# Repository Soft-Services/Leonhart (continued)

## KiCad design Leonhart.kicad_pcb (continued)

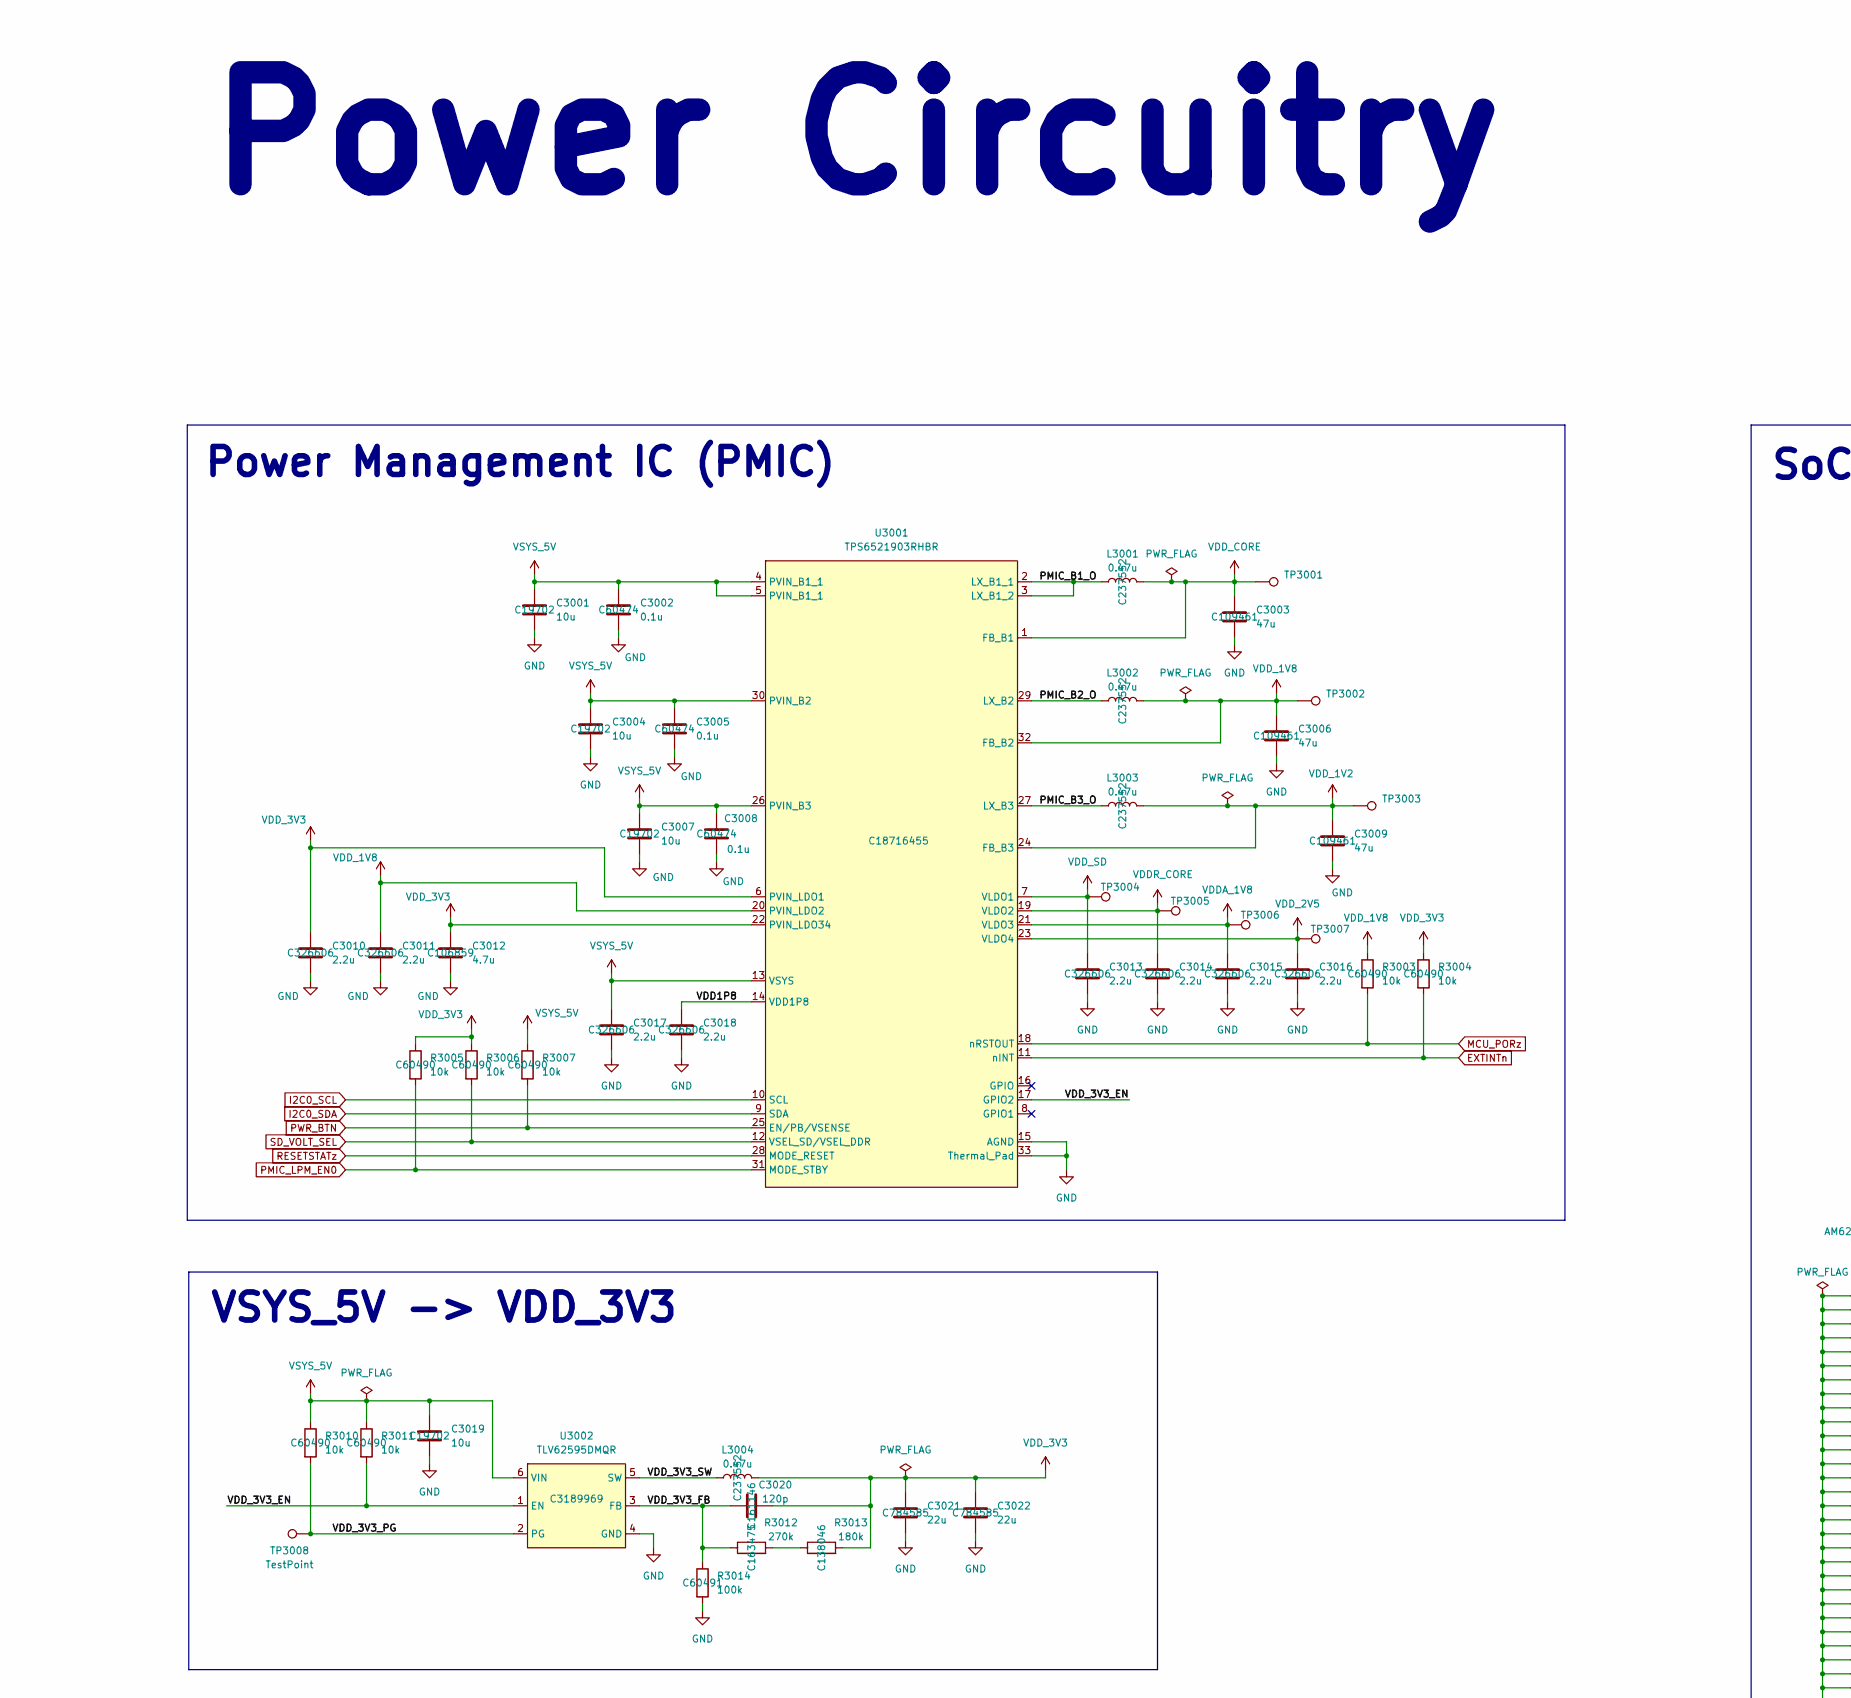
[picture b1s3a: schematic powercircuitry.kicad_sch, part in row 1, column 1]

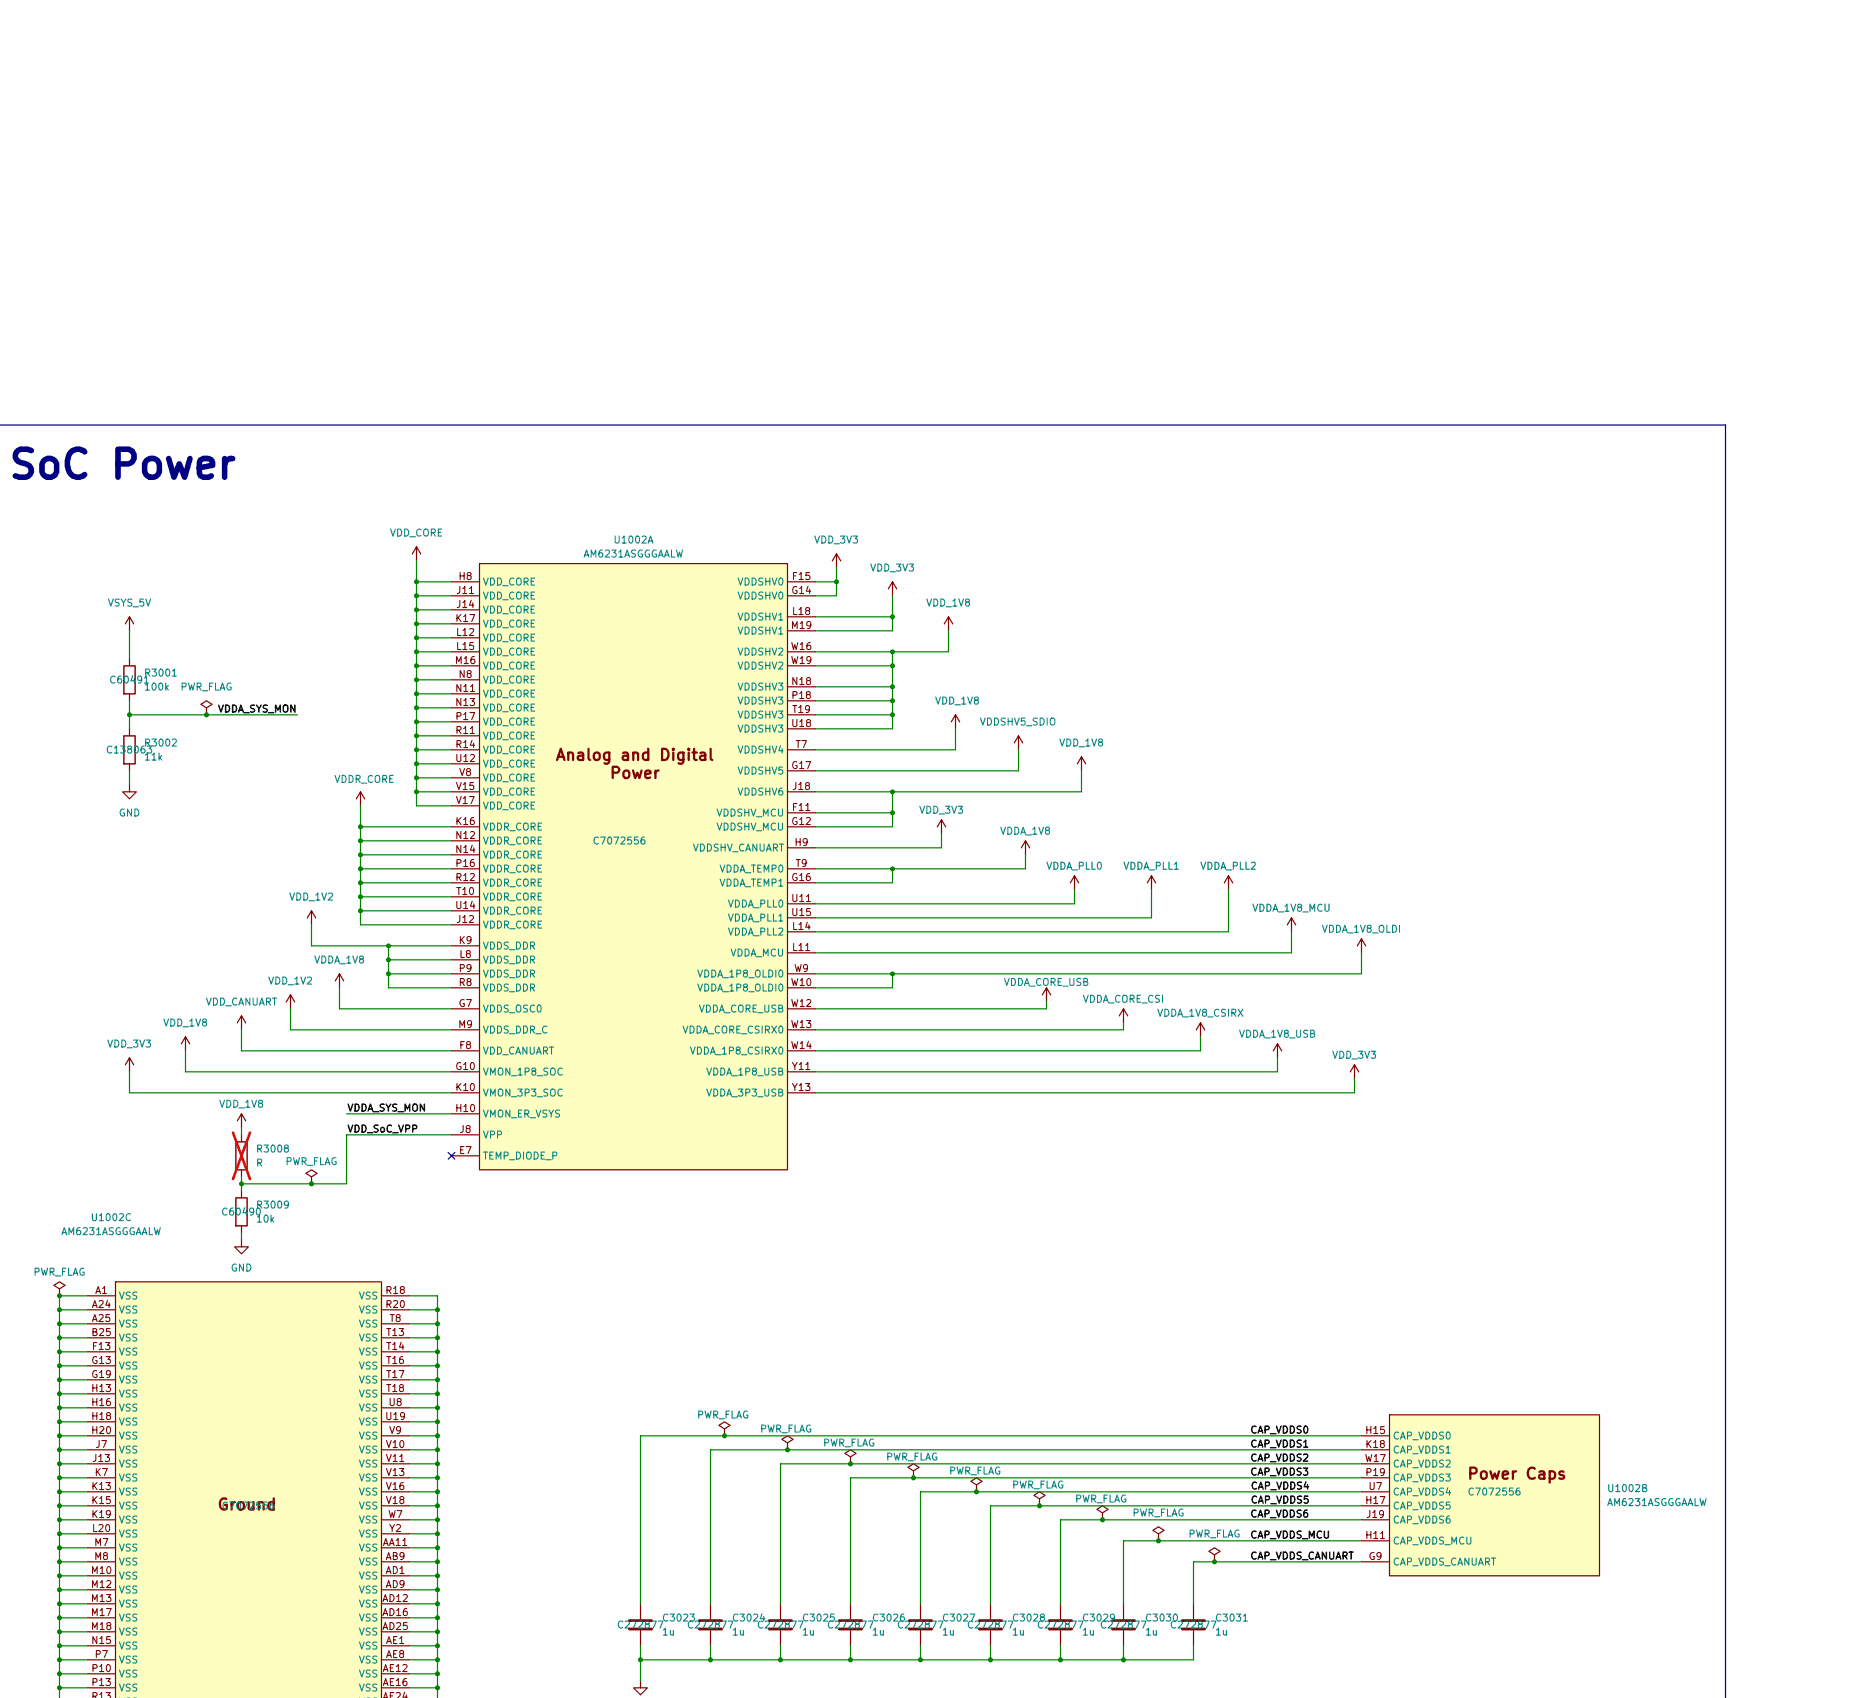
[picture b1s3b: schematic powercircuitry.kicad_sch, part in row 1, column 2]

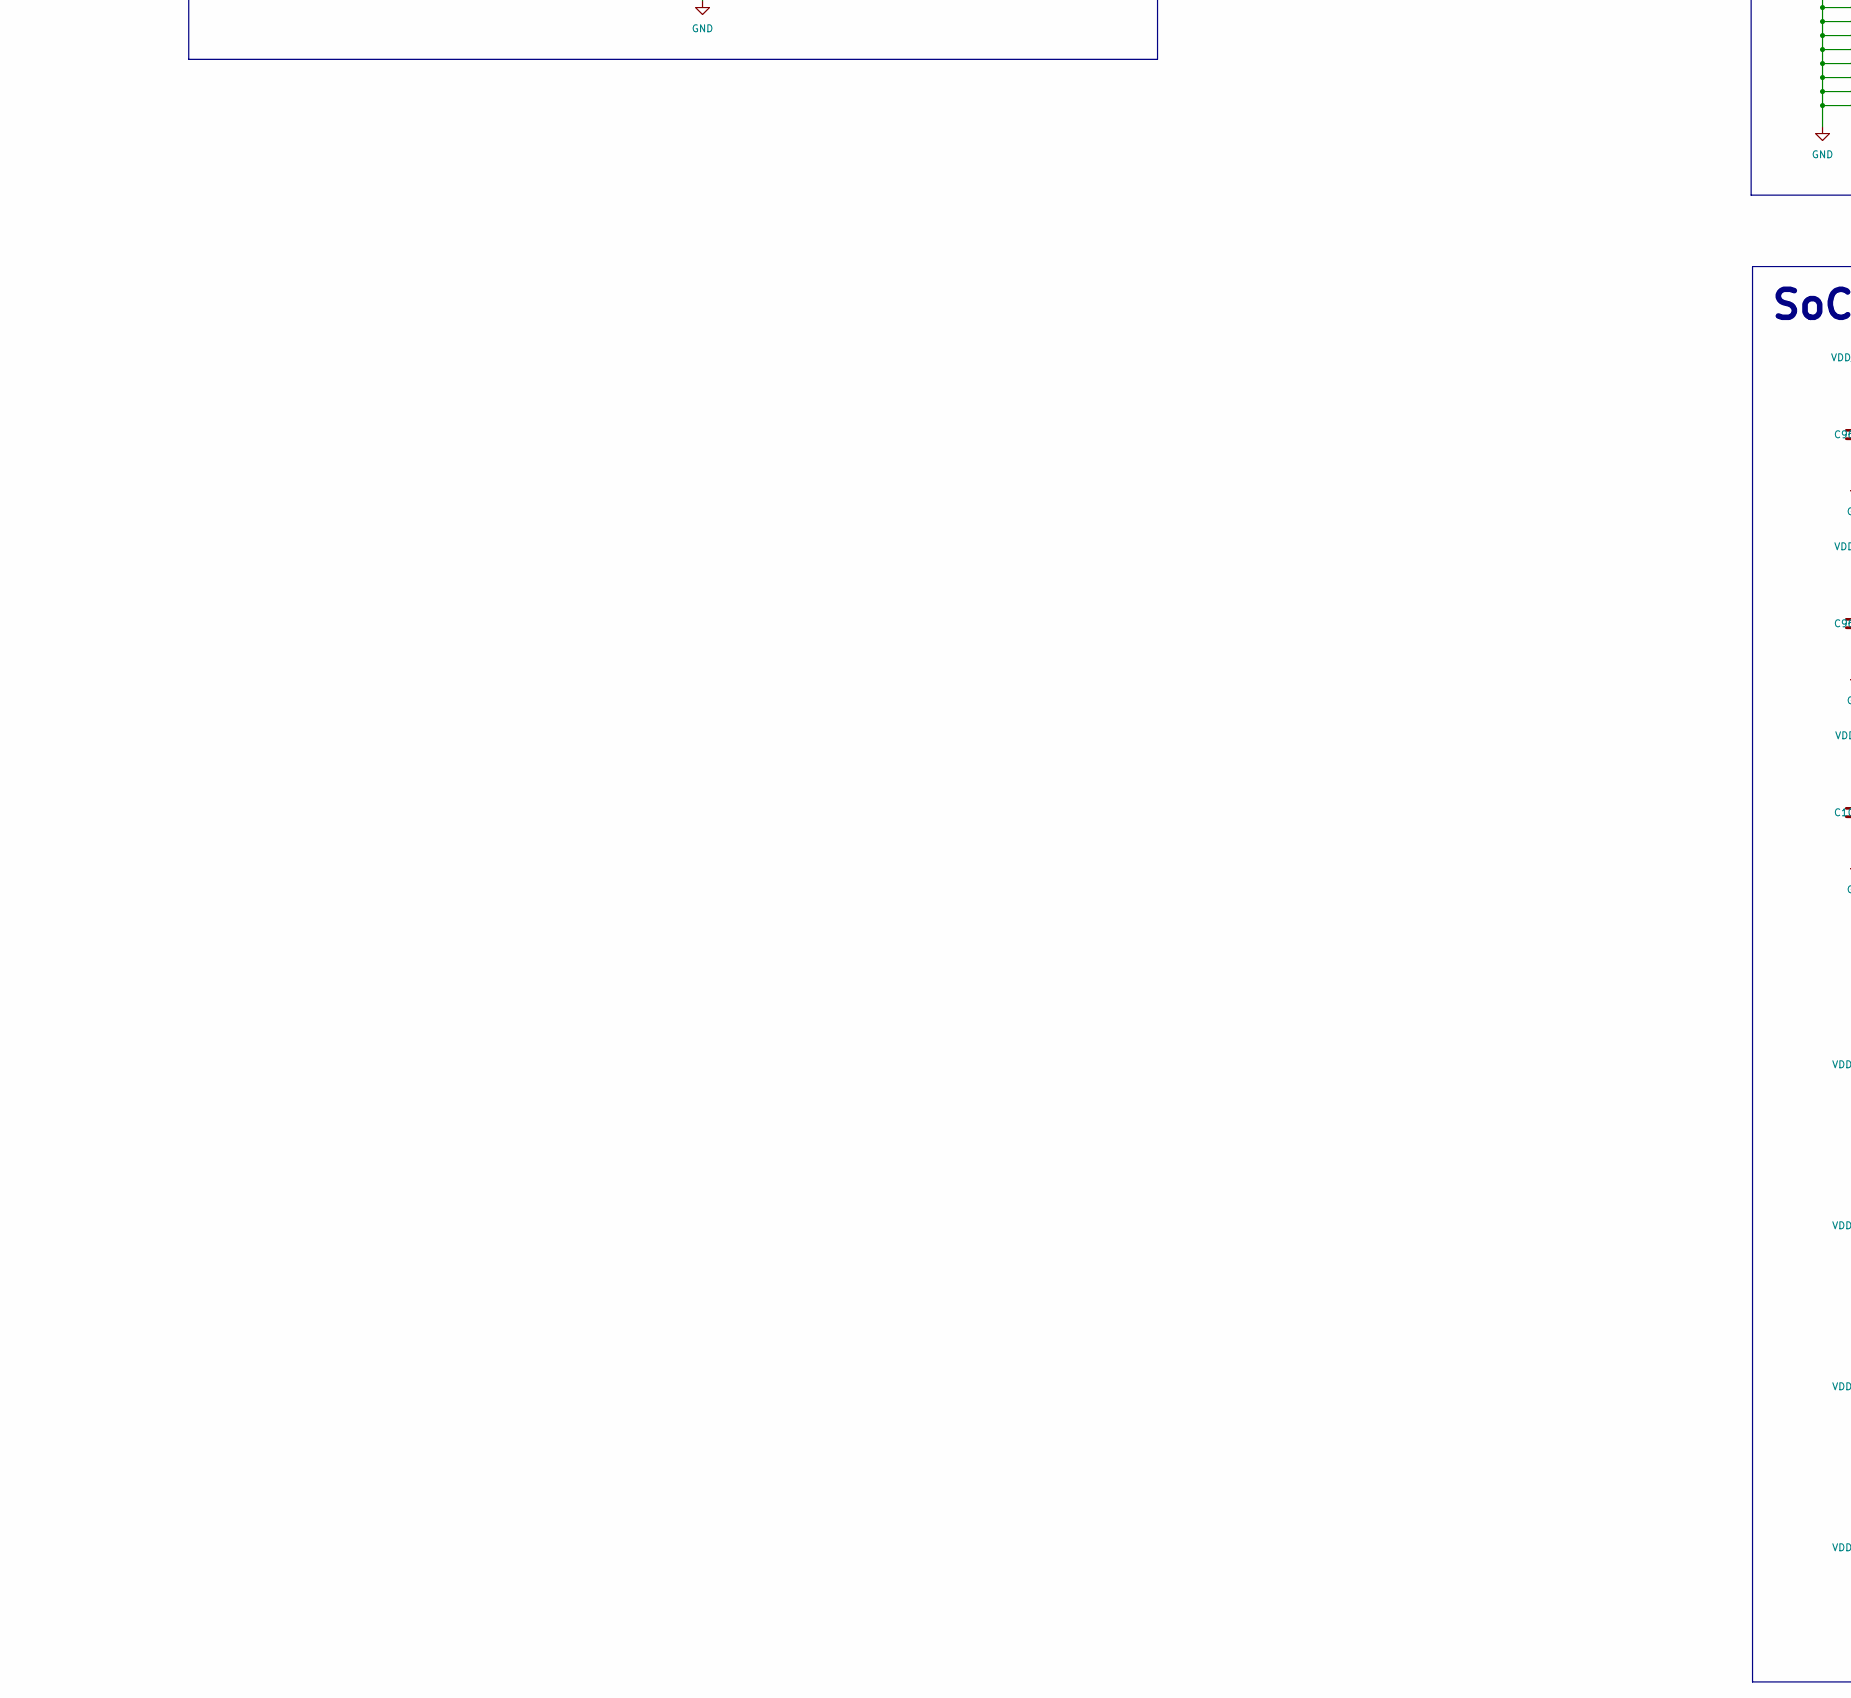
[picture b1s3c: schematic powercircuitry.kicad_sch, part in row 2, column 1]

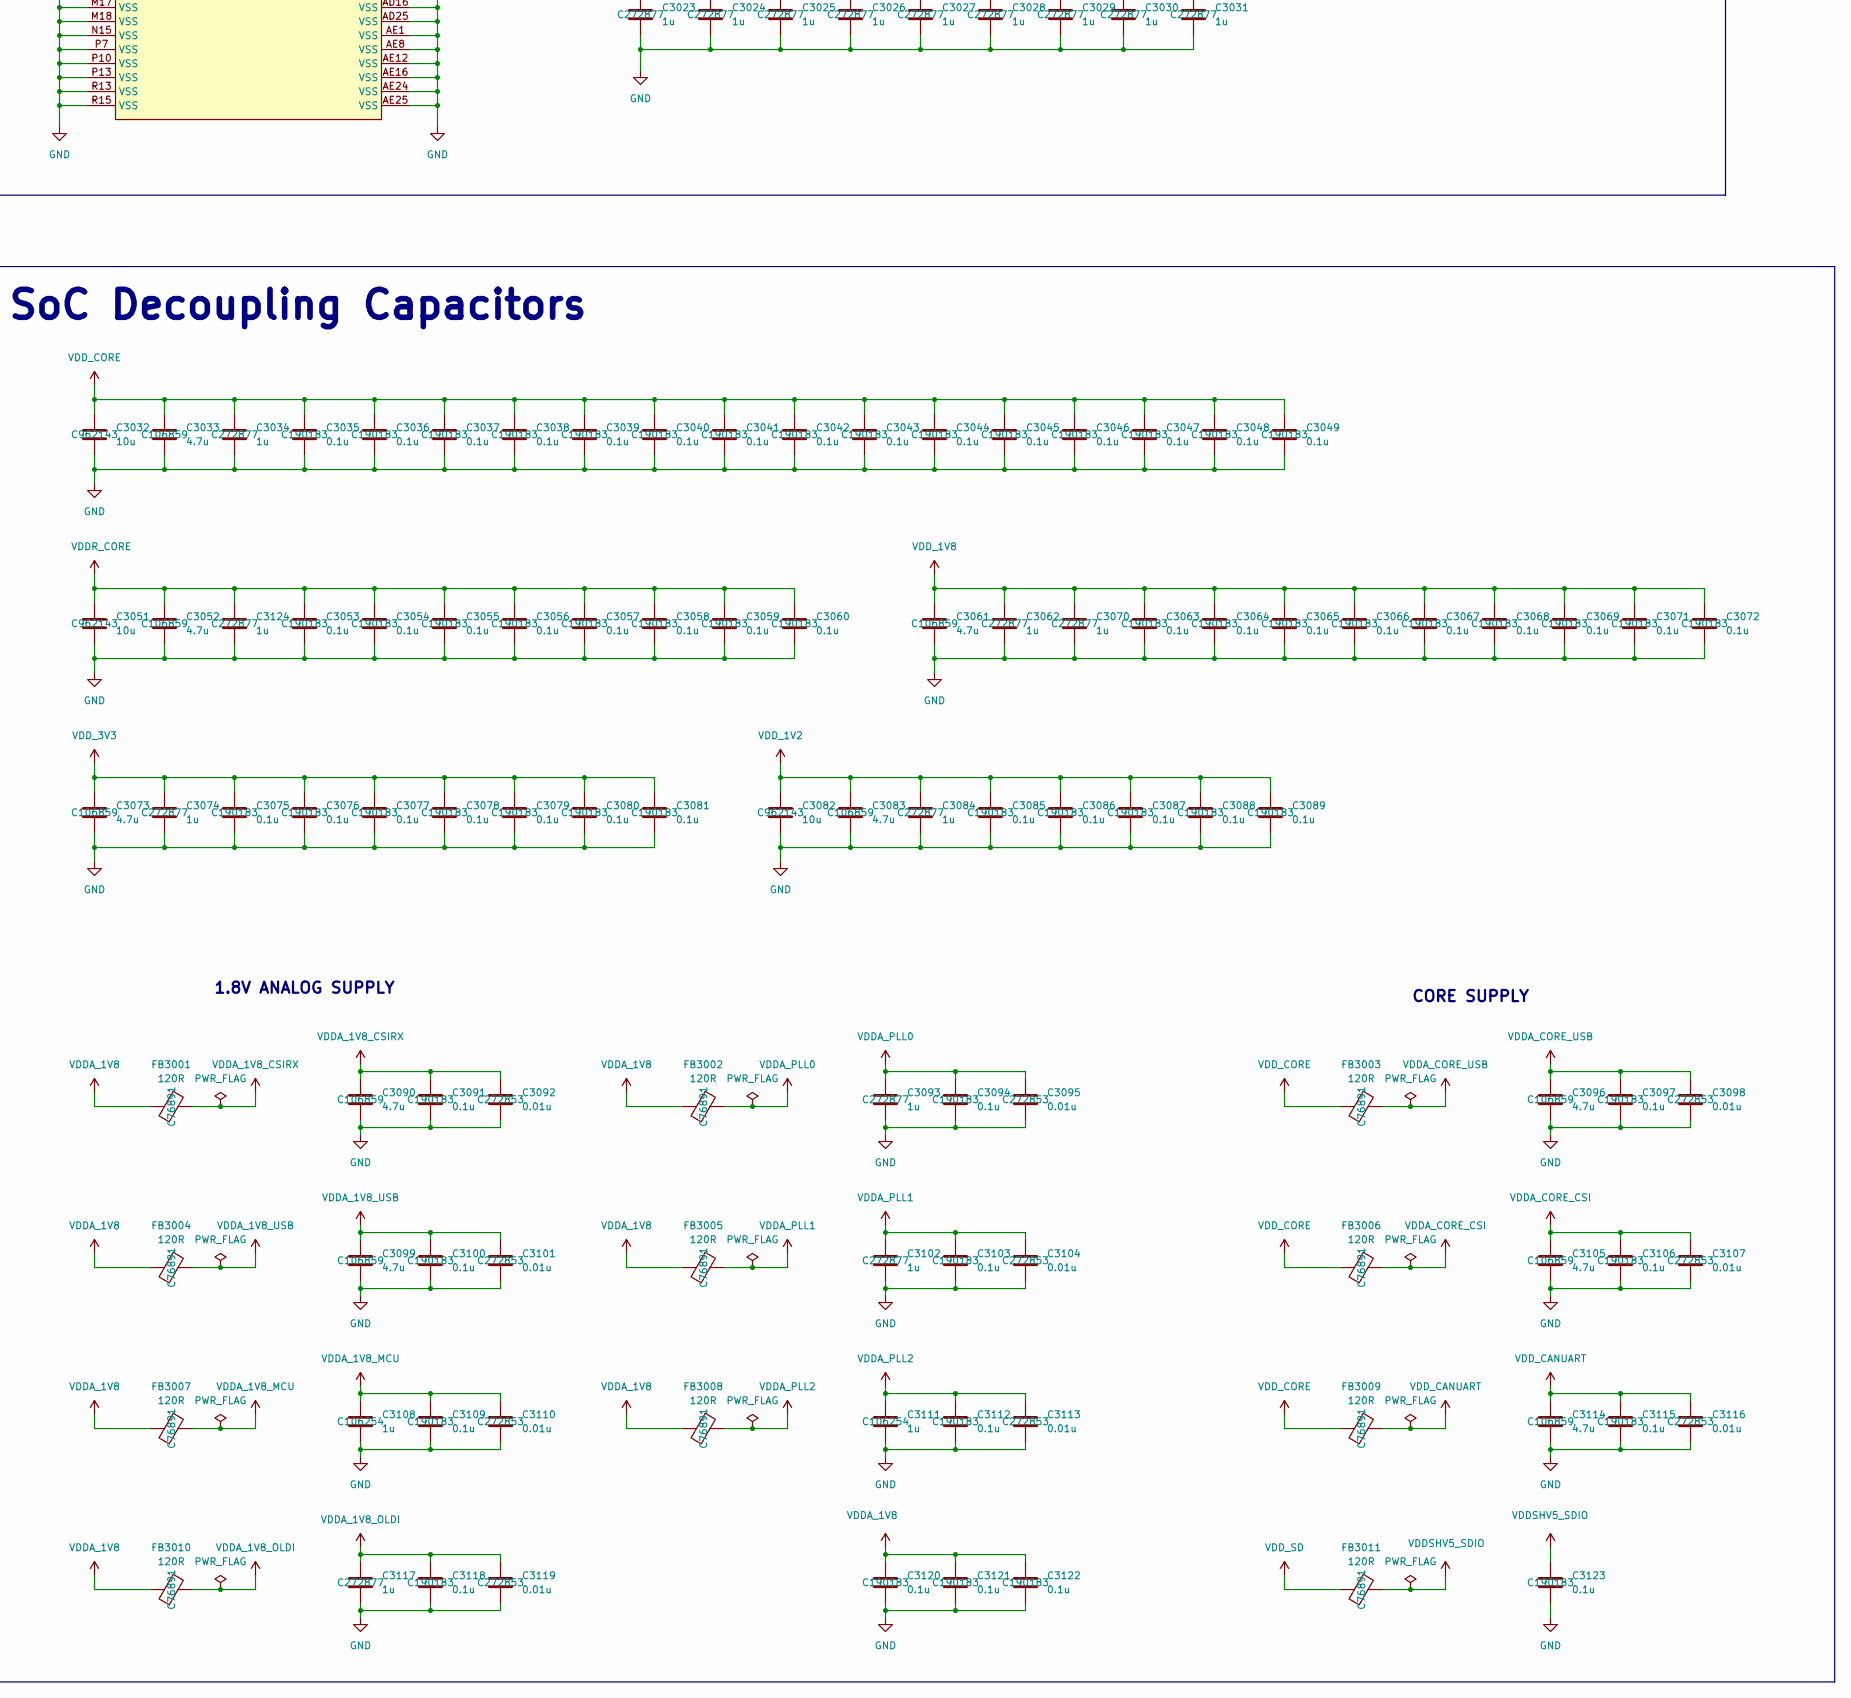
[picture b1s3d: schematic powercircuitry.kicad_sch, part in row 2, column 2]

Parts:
C3001, C3004, C3007, C3019: 10u; C_0603_1608Metric; JLCPCB Part# C19702
C3002, C3005, C3008: 0.1u; C_0402_1005Metric; JLCPCB Part# C60474
C3003, C3006, C3009: 47u; C_0805_2012Metric; JLCPCB Part# C109461
C3010, C3011, C3013, C3014, C3015, C3016, C3017, C3018: 2.2u; C_0402_1005Metric; JLCPCB Part# C326606
C3012, C3033, C3052, C3061, C3073, C3083, C3090, C3096, C3099, C3105, C3114: 4.7u; C_0402_1005Metric; JLCPCB Part# C106859
C3020: 120p; C_0402_1005Metric; JLCPCB Part# C161146
C3021, C3022: 22u; C_0805_2012Metric; JLCPCB Part# C784585
C3023, C3024, C3025, C3026, C3027, C3028, C3029, C3030, C3031, C3034, C3062, C3070, C3074, C3084, C3093, C3102, C3117: 1u; C_0201_0603Metric; JLCPCB Part# C272877
C3032, C3051, C3082: 10u; C_0402_1005Metric; JLCPCB Part# C962143
C3035, C3036, C3037, C3038, C3039, C3040, C3041, C3042, C3043, C3044, C3045, C3046, C3047, C3048, C3049, C3053, C3054, C3055, C3056, C3057, C3058, C3059, C3060, C3063, C3064, C3065, C3066, C3067, C3068, C3069, C3071, C3072, C3075, C3076, C3077, C3078, C3079, C3080, C3081, C3085, C3086, C3087, C3088, C3089, C3091, C3094, C3097, C3100, C3103, C3106, C3109, C3112, C3115, C3118, C3120, C3121, C3122, C3123: 0.1u; C_0201_0603Metric; JLCPCB Part# C190183
C3092, C3095, C3098, C3101, C3104, C3107, C3110, C3113, C3116, C3119: 0.01u; C_0201_0603Metric; JLCPCB Part# C272853
C3108, C3111: 1u; C_0402_1005Metric; JLCPCB Part# C106254
C3124: 1u; 0201_Cap_Leonhart; JLCPCB Part# C272877
FB3001, FB3002, FB3003, FB3004, FB3005, FB3006, FB3007, FB3008, FB3009, FB3010, FB3011: 120R; R_0402_1005Metric; JLCPCB Part# C76891
L3001, L3002, L3003, L3004: 0.47u; L_1008_2520Metric; JLCPCB Part# C237552
R3001, R3014: 100k; R_0402_1005Metric; JLCPCB Part# C60491
R3002: 11k; R_0402_1005Metric; JLCPCB Part# C138063
R3003, R3004, R3005, R3006, R3007, R3009, R3010, R3011: 10k; R_0402_1005Metric; JLCPCB Part# C60490
R3008: R; R_0402_1005Metric; not fitted
R3012: 270k; R_0402_1005Metric; JLCPCB Part# C163475
R3013: 180k; R_0402_1005Metric; JLCPCB Part# C138046
TP3001, TP3002, TP3003, TP3004, TP3005, TP3006, TP3007, TP3008: TestPoint; TestPoint_Pad_1.0x1.0mm
U1002: AM6231ASGGGAALW; BGA425C50P25X25_1300X1300X89; JLCPCB Part# C7072556
U3001: TPS6521903RHBR; QFN50P500X500X100-33N-D; JLCPCB Part# C18716455
U3002: TLV62595DMQR; JLCPCB Part# C3189969

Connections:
/Power Circuitry [3]/CAP_VDDS0: C3023.1, U1002.H15 (CAP_VDDS0)
/Power Circuitry [3]/CAP_VDDS1: C3024.1, U1002.K18 (CAP_VDDS1)
/Power Circuitry [3]/CAP_VDDS2: C3025.1, U1002.W17 (CAP_VDDS2)
/Power Circuitry [3]/CAP_VDDS3: C3026.1, U1002.P19 (CAP_VDDS3)
/Power Circuitry [3]/CAP_VDDS4: C3027.1, U1002.U7 (CAP_VDDS4)
/Power Circuitry [3]/CAP_VDDS5: C3028.1, U1002.H17 (CAP_VDDS5)
/Power Circuitry [3]/CAP_VDDS6: C3029.1, U1002.J19 (CAP_VDDS6)
/Power Circuitry [3]/CAP_VDDS_CANUART: C3031.1, U1002.G9 (CAP_VDDS_CANUART)
/Power Circuitry [3]/CAP_VDDS_MCU: C3030.1, U1002.H11 (CAP_VDDS_MCU)
/Power Circuitry [3]/PMIC_B1_O: L3001.1, U3001.2 (LX_B1_1), U3001.3 (LX_B1_2)
/Power Circuitry [3]/PMIC_B2_O: L3002.1, U3001.29 (LX_B2)
/Power Circuitry [3]/PMIC_B3_O: L3003.1, U3001.27 (LX_B3)
/Power Circuitry [3]/VDD1P8: C3018.1, U3001.14 (VDD1P8)
/Power Circuitry [3]/VDDA_SYS_MON: R3001.2, R3002.1, U1002.H10 (VMON_ER_VSYS)
/Power Circuitry [3]/VDD_3V3_EN: R3011.2, U3001.17 (GPIO2), U3002.1 (EN)
/Power Circuitry [3]/VDD_3V3_FB: C3020.1, R3012.1, R3014.1, U3002.3 (FB)
/Power Circuitry [3]/VDD_3V3_PG: R3010.2, TP3008.1, U3002.2 (PG); also elsewhere on the board
/Power Circuitry [3]/VDD_3V3_SW: L3004.1, U3002.5 (SW)
/Power Circuitry [3]/VDD_SoC_VPP: R3008.2, R3009.1, U1002.J8 (VPP)
EXTINTn: R3004.2, U3001.11 (nINT); also elsewhere on the board
GND: C3001.2, C3002.2, C3003.2, C3004.2, C3005.2, C3006.2, C3007.2, C3008.2, C3009.2, C3010.2, C3011.2, C3012.2, C3013.2, C3014.2, C3015.2, C3016.2, C3017.2, C3018.2, C3019.2, C3021.2, C3022.2, C3023.2, C3024.2, C3025.2, C3026.2, C3027.2, C3028.2, C3029.2, C3030.2, C3031.2, C3032.2, C3033.2, C3034.2, C3035.2, C3036.2, C3037.2, C3038.2, C3039.2, C3040.2, C3041.2, C3042.2, C3043.2, C3044.2, C3045.2, C3046.2, C3047.2, C3048.2, C3049.2, C3051.2, C3052.2, C3053.2, C3054.2, C3055.2, C3056.2, C3057.2, C3058.2, C3059.2, C3060.2, C3061.2, C3062.2, C3063.2, C3064.2, C3065.2, C3066.2, C3067.2, C3068.2, C3069.2, C3070.2, C3071.2, C3072.2, C3073.2, C3074.2, C3075.2, C3076.2, C3077.2, C3078.2, C3079.2, C3080.2, C3081.2, C3082.2, C3083.2, C3084.2, C3085.2, C3086.2, C3087.2, C3088.2, C3089.2, C3090.2, C3091.2, C3092.2, C3093.2, C3094.2, C3095.2, C3096.2, C3097.2, C3098.2, C3099.2, C3100.2, C3101.2, C3102.2, C3103.2, C3104.2, C3105.2, C3106.2, C3107.2, C3108.2, C3109.2, C3110.2, C3111.2, C3112.2, C3113.2, C3114.2, C3115.2, C3116.2, C3117.2, C3118.2, C3119.2, C3120.2, C3121.2, C3122.2, C3123.2, C3124.2, R3002.2, R3009.2, R3014.2, U1002.A1 (VSS), U1002.A24 (VSS), U1002.A25 (VSS), U1002.AA11 (VSS), U1002.AB9 (VSS), U1002.AD1 (VSS), U1002.AD9 (VSS), U1002.AD12 (VSS), U1002.AD16 (VSS), U1002.AD25 (VSS), U1002.AE1 (VSS), U1002.AE8 (VSS), U1002.AE12 (VSS), U1002.AE16 (VSS), U1002.AE24 (VSS), U1002.AE25 (VSS), U1002.B25 (VSS), U1002.F13 (VSS), U1002.G13 (VSS), U1002.G19 (VSS), U1002.H13 (VSS), U1002.H16 (VSS), U1002.H18 (VSS), U1002.H20 (VSS), U1002.J7 (VSS), U1002.J13 (VSS), U1002.K7 (VSS), U1002.K13 (VSS), U1002.K15 (VSS), U1002.K19 (VSS), U1002.L20 (VSS), U1002.M7 (VSS), U1002.M8 (VSS), U1002.M10 (VSS), U1002.M12 (VSS), U1002.M13 (VSS), U1002.M17 (VSS), U1002.M18 (VSS), U1002.N15 (VSS), U1002.P7 (VSS), U1002.P10 (VSS), U1002.P13 (VSS), U1002.R13 (VSS), U1002.R15 (VSS), U1002.R18 (VSS), U1002.R20 (VSS), U1002.T8 (VSS), U1002.T13 (VSS), U1002.T14 (VSS), U1002.T16 (VSS), U1002.T17 (VSS), U1002.T18 (VSS), U1002.U8 (VSS), U1002.U19 (VSS), U1002.V9 (VSS), U1002.V10 (VSS), U1002.V11 (VSS), U1002.V13 (VSS), U1002.V16 (VSS), U1002.V18 (VSS), U1002.W7 (VSS), U1002.Y2 (VSS), U3001.15 (AGND), U3001.33 (Thermal_Pad), U3002.4 (GND); also elsewhere on the board
I2C0_SCL: U3001.10 (SCL); also elsewhere on the board
I2C0_SDA: U3001.9 (SDA); also elsewhere on the board
MCU_PORz: R3003.2, U3001.18 (nRSTOUT); also elsewhere on the board
unnamed: R3012.2, R3013.1
PMIC_LPM_EN0: R3005.2, U3001.31 (MODE_STBY); also elsewhere on the board
PWR_BTN: R3007.2, U3001.25 (EN/PB/VSENSE); also elsewhere on the board
RESETSTATz: U3001.28 (MODE_RESET); also elsewhere on the board
SD_VOLT_SEL: R3006.2, U3001.12 (VSEL_SD/VSEL_DDR); also elsewhere on the board
VDDA_1V8: C3015.1, C3120.1, C3121.1, C3122.1, FB3001.1, FB3002.1, FB3004.1, FB3005.1, FB3007.1, FB3008.1, FB3010.1, TP3006.1, U1002.G7 (VDDS_OSC0), U1002.G16 (VDDA_TEMP1), U1002.T9 (VDDA_TEMP0), U3001.21 (VLDO3); also elsewhere on the board
VDDA_1V8_CSIRX: C3090.1, C3091.1, C3092.1, FB3001.2, U1002.W14 (VDDA_1P8_CSIRX0)
VDDA_1V8_MCU: C3108.1, C3109.1, C3110.1, FB3007.2, U1002.L11 (VDDA_MCU)
VDDA_1V8_OLDI: C3117.1, C3118.1, C3119.1, FB3010.2, U1002.W9 (VDDA_1P8_OLDI0), U1002.W10 (VDDA_1P8_OLDI0)
VDDA_1V8_USB: C3099.1, C3100.1, C3101.1, FB3004.2, U1002.Y11 (VDDA_1P8_USB)
VDDA_CORE_CSI: C3105.1, C3106.1, C3107.1, FB3006.2, U1002.W13 (VDDA_CORE_CSIRX0)
VDDA_CORE_USB: C3096.1, C3097.1, C3098.1, FB3003.2, U1002.W12 (VDDA_CORE_USB)
VDDA_PLL0: C3093.1, C3094.1, C3095.1, FB3002.2, U1002.U11 (VDDA_PLL0)
VDDA_PLL1: C3102.1, C3103.1, C3104.1, FB3005.2, U1002.U15 (VDDA_PLL1)
VDDA_PLL2: C3111.1, C3112.1, C3113.1, FB3008.2, U1002.L14 (VDDA_PLL2)
VDDR_CORE: C3014.1, C3051.1, C3052.1, C3053.1, C3054.1, C3055.1, C3056.1, C3057.1, C3058.1, C3059.1, C3060.1, C3124.1, TP3005.1, U1002.J12 (VDDR_CORE), U1002.K16 (VDDR_CORE), U1002.N12 (VDDR_CORE), U1002.N14 (VDDR_CORE), U1002.P16 (VDDR_CORE), U1002.R12 (VDDR_CORE), U1002.T10 (VDDR_CORE), U1002.U14 (VDDR_CORE), U3001.19 (VLDO2); also elsewhere on the board
VDDSHV5_SDIO: C3123.1, FB3011.2, U1002.G17 (VDDSHV5)
VDD_1V2: C3009.1, C3082.1, C3083.1, C3084.1, C3085.1, C3086.1, C3087.1, C3088.1, C3089.1, L3003.2, TP3003.1, U1002.K9 (VDDS_DDR), U1002.L8 (VDDS_DDR), U1002.M9 (VDDS_DDR_C), U1002.P9 (VDDS_DDR), U1002.R8 (VDDS_DDR), U3001.24 (FB_B3); also elsewhere on the board
VDD_1V8: C3006.1, C3011.1, C3061.1, C3062.1, C3063.1, C3064.1, C3065.1, C3066.1, C3067.1, C3068.1, C3069.1, C3070.1, C3071.1, C3072.1, L3002.2, R3003.1, R3008.1, TP3002.1, U1002.F11 (VDDSHV_MCU), U1002.G10 (VMON_1P8_SOC), U1002.G12 (VDDSHV_MCU), U1002.J18 (VDDSHV6), U1002.N18 (VDDSHV3), U1002.P18 (VDDSHV3), U1002.T7 (VDDSHV4), U1002.T19 (VDDSHV3), U1002.U18 (VDDSHV3), U1002.W16 (VDDSHV2), U1002.W19 (VDDSHV2), U3001.20 (PVIN_LDO2), U3001.32 (FB_B2); also elsewhere on the board
VDD_2V5: C3016.1, TP3007.1, U3001.23 (VLDO4); also elsewhere on the board
VDD_3V3: C3010.1, C3012.1, C3020.2, C3021.1, C3022.1, C3073.1, C3074.1, C3075.1, C3076.1, C3077.1, C3078.1, C3079.1, C3080.1, C3081.1, L3004.2, R3004.1, R3005.1, R3006.1, R3013.2, U1002.F15 (VDDSHV0), U1002.G14 (VDDSHV0), U1002.H9 (VDDSHV_CANUART), U1002.K10 (VMON_3P3_SOC), U1002.L18 (VDDSHV1), U1002.M19 (VDDSHV1), U1002.Y13 (VDDA_3P3_USB), U3001.6 (PVIN_LDO1), U3001.22 (PVIN_LDO34); also elsewhere on the board
VDD_CANUART: C3114.1, C3115.1, C3116.1, FB3009.2, U1002.F8 (VDD_CANUART)
VDD_CORE: C3003.1, C3032.1, C3033.1, C3034.1, C3035.1, C3036.1, C3037.1, C3038.1, C3039.1, C3040.1, C3041.1, C3042.1, C3043.1, C3044.1, C3045.1, C3046.1, C3047.1, C3048.1, C3049.1, FB3003.1, FB3006.1, FB3009.1, L3001.2, TP3001.1, U1002.H8 (VDD_CORE), U1002.J11 (VDD_CORE), U1002.J14 (VDD_CORE), U1002.K17 (VDD_CORE), U1002.L12 (VDD_CORE), U1002.L15 (VDD_CORE), U1002.M16 (VDD_CORE), U1002.N8 (VDD_CORE), U1002.N11 (VDD_CORE), U1002.N13 (VDD_CORE), U1002.P17 (VDD_CORE), U1002.R11 (VDD_CORE), U1002.R14 (VDD_CORE), U1002.U12 (VDD_CORE), U1002.V8 (VDD_CORE), U1002.V15 (VDD_CORE), U1002.V17 (VDD_CORE), U3001.1 (FB_B1); also elsewhere on the board
VDD_SD: C3013.1, FB3011.1, TP3004.1, U3001.7 (VLDO1); also elsewhere on the board
VSYS_5V: C3001.1, C3002.1, C3004.1, C3005.1, C3007.1, C3008.1, C3017.1, C3019.1, R3001.1, R3007.1, R3010.1, R3011.1, U3001.4 (PVIN_B1_1), U3001.5 (PVIN_B1_1), U3001.13 (VSYS), U3001.26 (PVIN_B3), U3001.30 (PVIN_B2), U3002.6 (VIN); also elsewhere on the board

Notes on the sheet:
SoC Decoupling Capacitors
Power Management IC (PMIC)
SoC Power
VSYS_5V -> VDD_3V3
CORE SUPPLY
Power Circuitry
1.8V ANALOG SUPPLY
